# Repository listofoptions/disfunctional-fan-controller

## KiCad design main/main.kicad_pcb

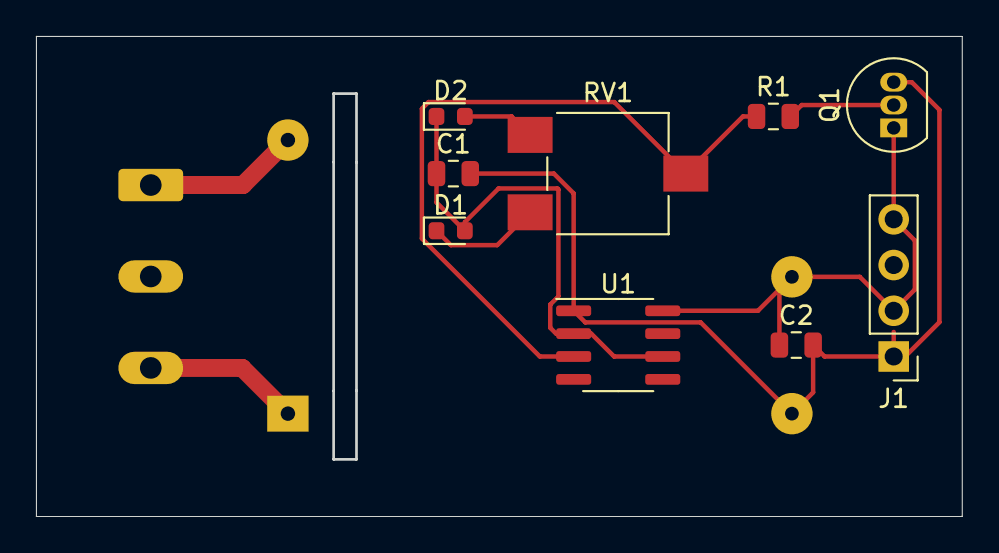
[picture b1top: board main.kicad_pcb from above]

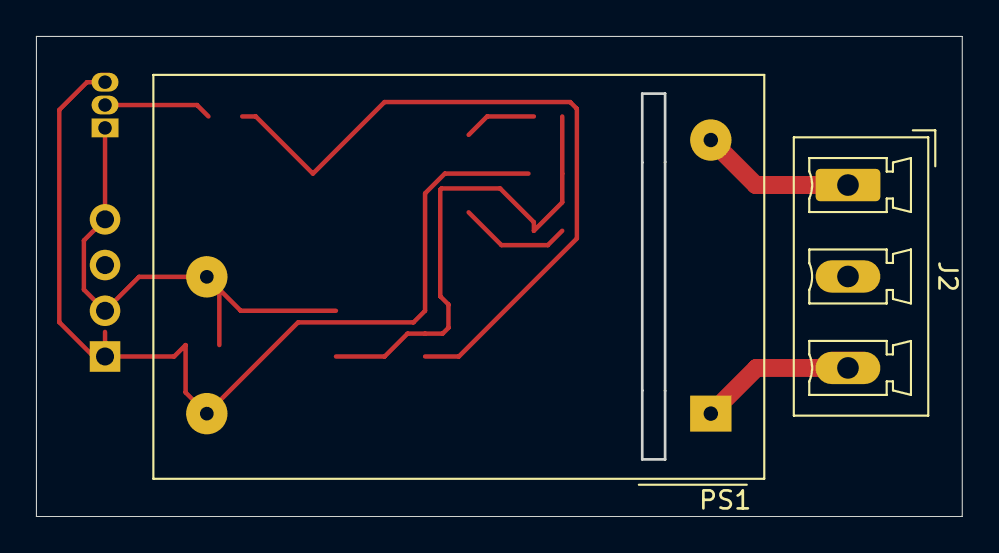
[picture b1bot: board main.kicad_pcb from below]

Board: 2 copper layers, 51.4 x 26.7 mm, 11 parts (2 on the bottom side), 9 nets.

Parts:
C1: 4N7; C_0805_2012Metric
C2: 1U; C_0805_2012Metric
D1, D2: 1N4148; D_0603_1608Metric
J1: Molex 47054-1000; PinHeader_1x04_P2.54mm_Vertical
J2: AC MAINS; PhoenixContact_MCV_1,5_3-G-5.08_1x03_P5.08mm_Vertical
PS1: IRM-02-12; Converter_ACDC_MeanWell_IRM-02-xx_THT
Q1: BC547; TO-92_Inline
R1: 10K; R_0805_2012Metric
RV1: 10K; Potentiometer_ACP_CA6-VSMD_Vertical
U1: ICM7555xB; SOIC-8_3.9x4.9mm_P1.27mm

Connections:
unnamed: C1.1, D1.2, D2.1, U1.2, U1.6
unnamed: C1.2, C2.2, J1.1, PS1.3, Q1.3, U1.1
unnamed: C2.1, J1.2, J1.4, PS1.4, Q1.1, U1.8
unnamed: D1.1, RV1.1
unnamed: D2.2, RV1.3
unnamed: J2.1, PS1.2
unnamed: J2.3, PS1.1
unnamed: Q1.2, R1.2
unnamed: R1.1, RV1.2, U1.3

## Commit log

2021-04-22 initial commit, todo better layout
2021-04-23 simpler power supply, and slightly better layout
2021-04-23 simpler dumber fan controller, will add pwm feedback and temp sensing later
